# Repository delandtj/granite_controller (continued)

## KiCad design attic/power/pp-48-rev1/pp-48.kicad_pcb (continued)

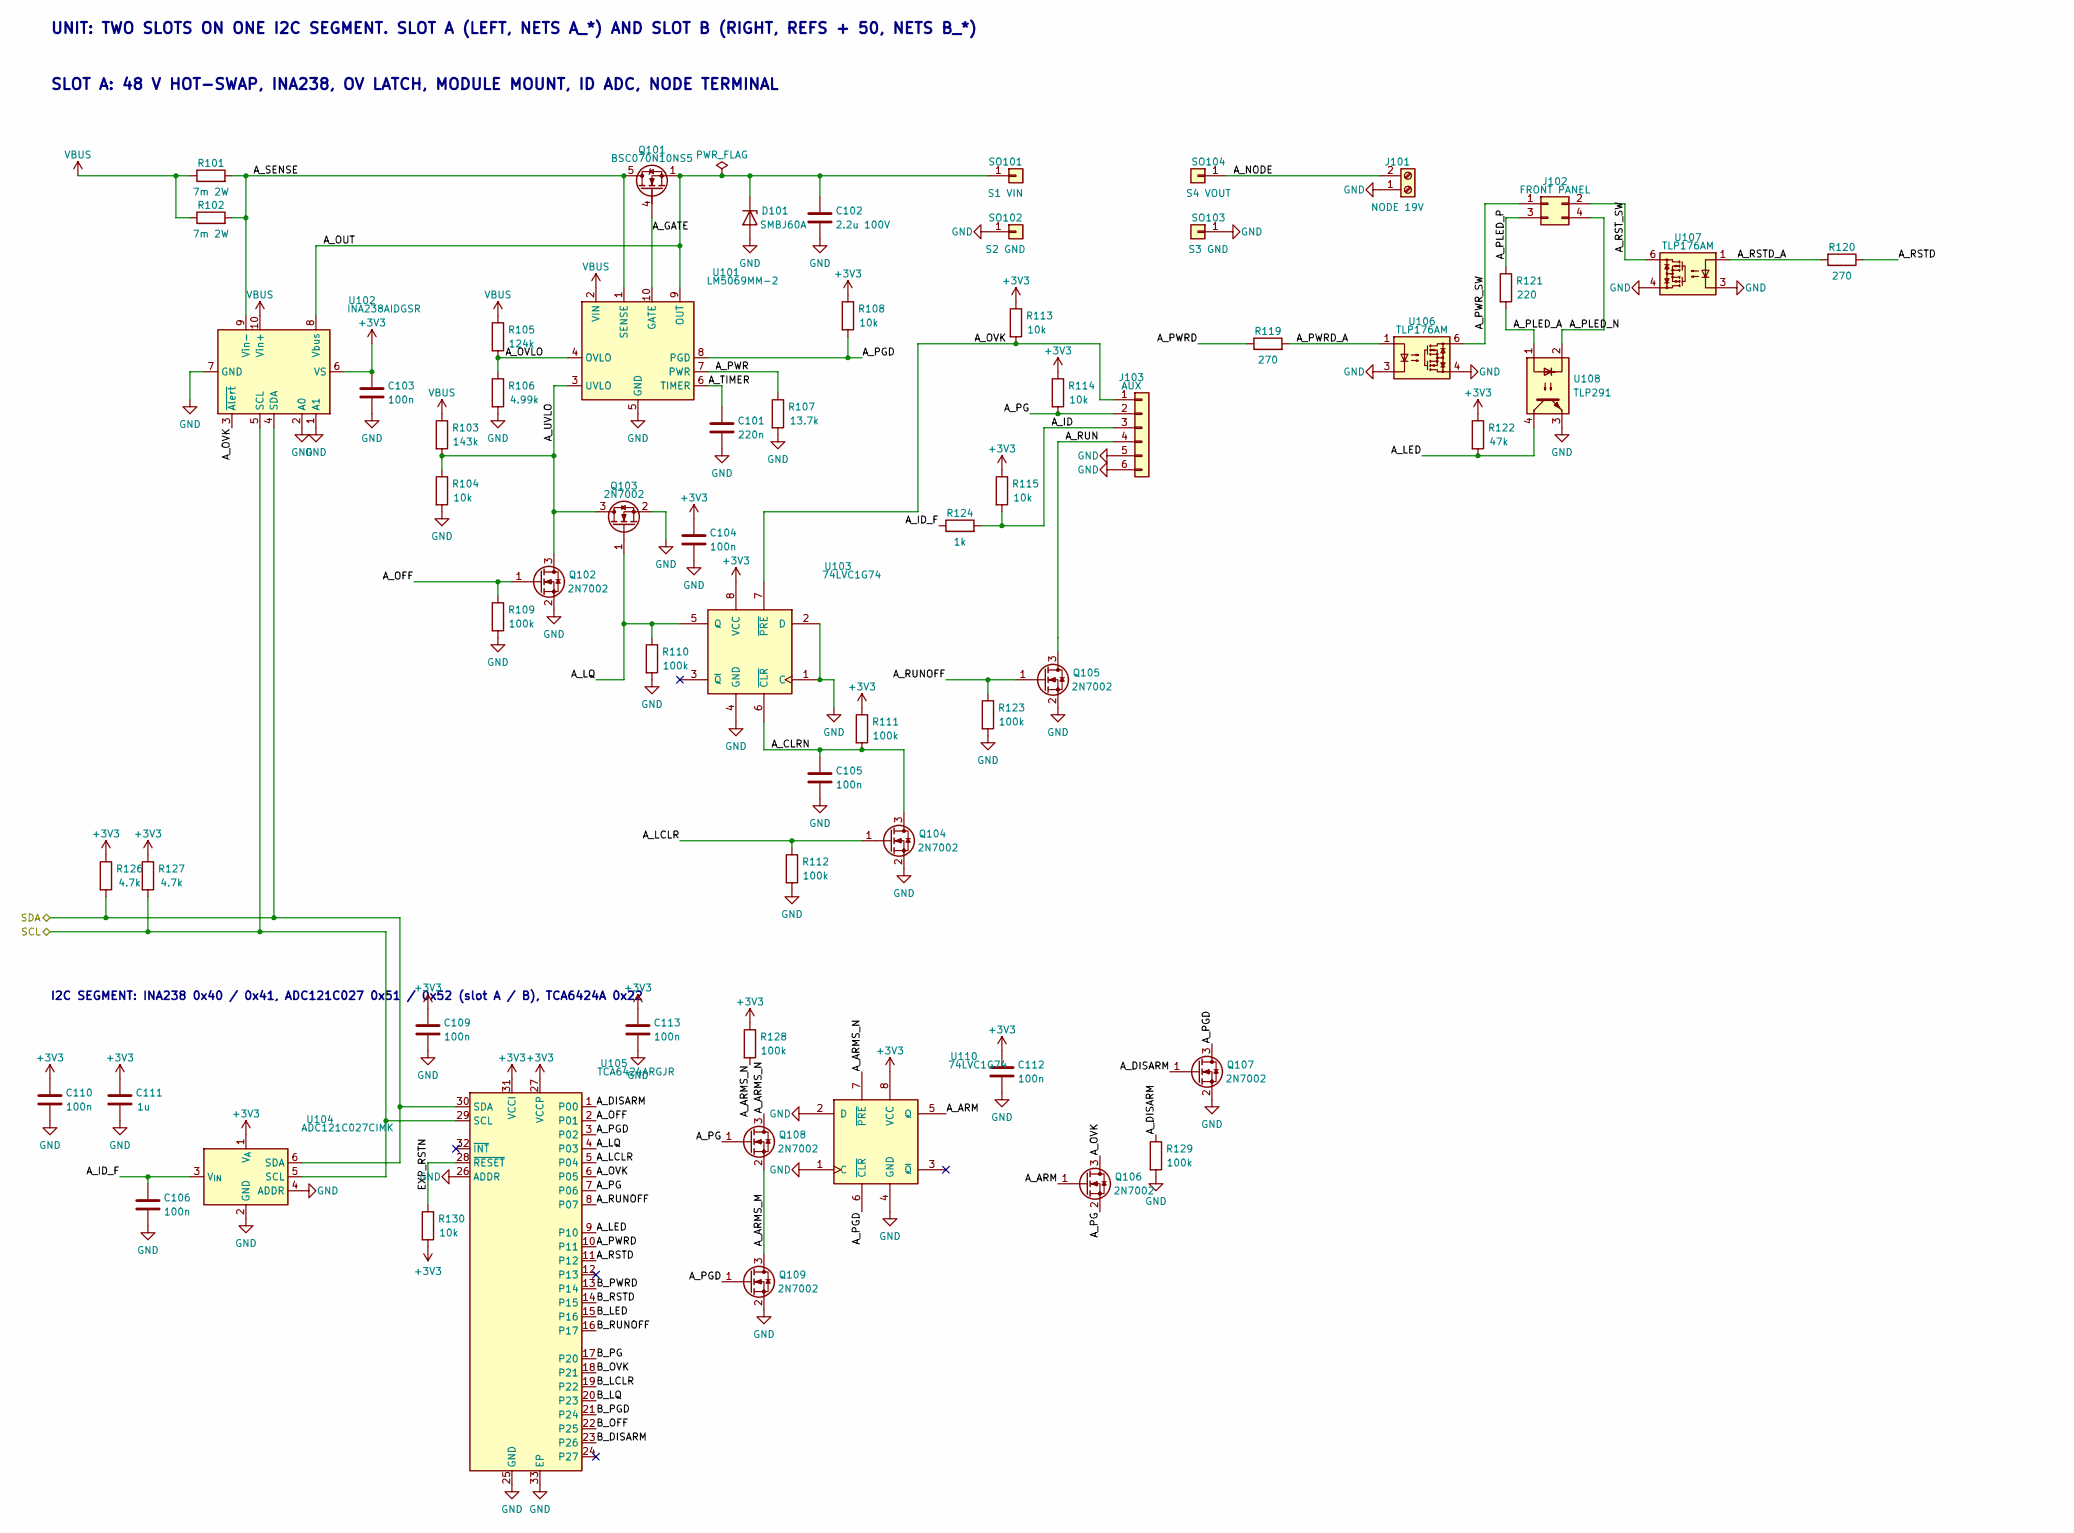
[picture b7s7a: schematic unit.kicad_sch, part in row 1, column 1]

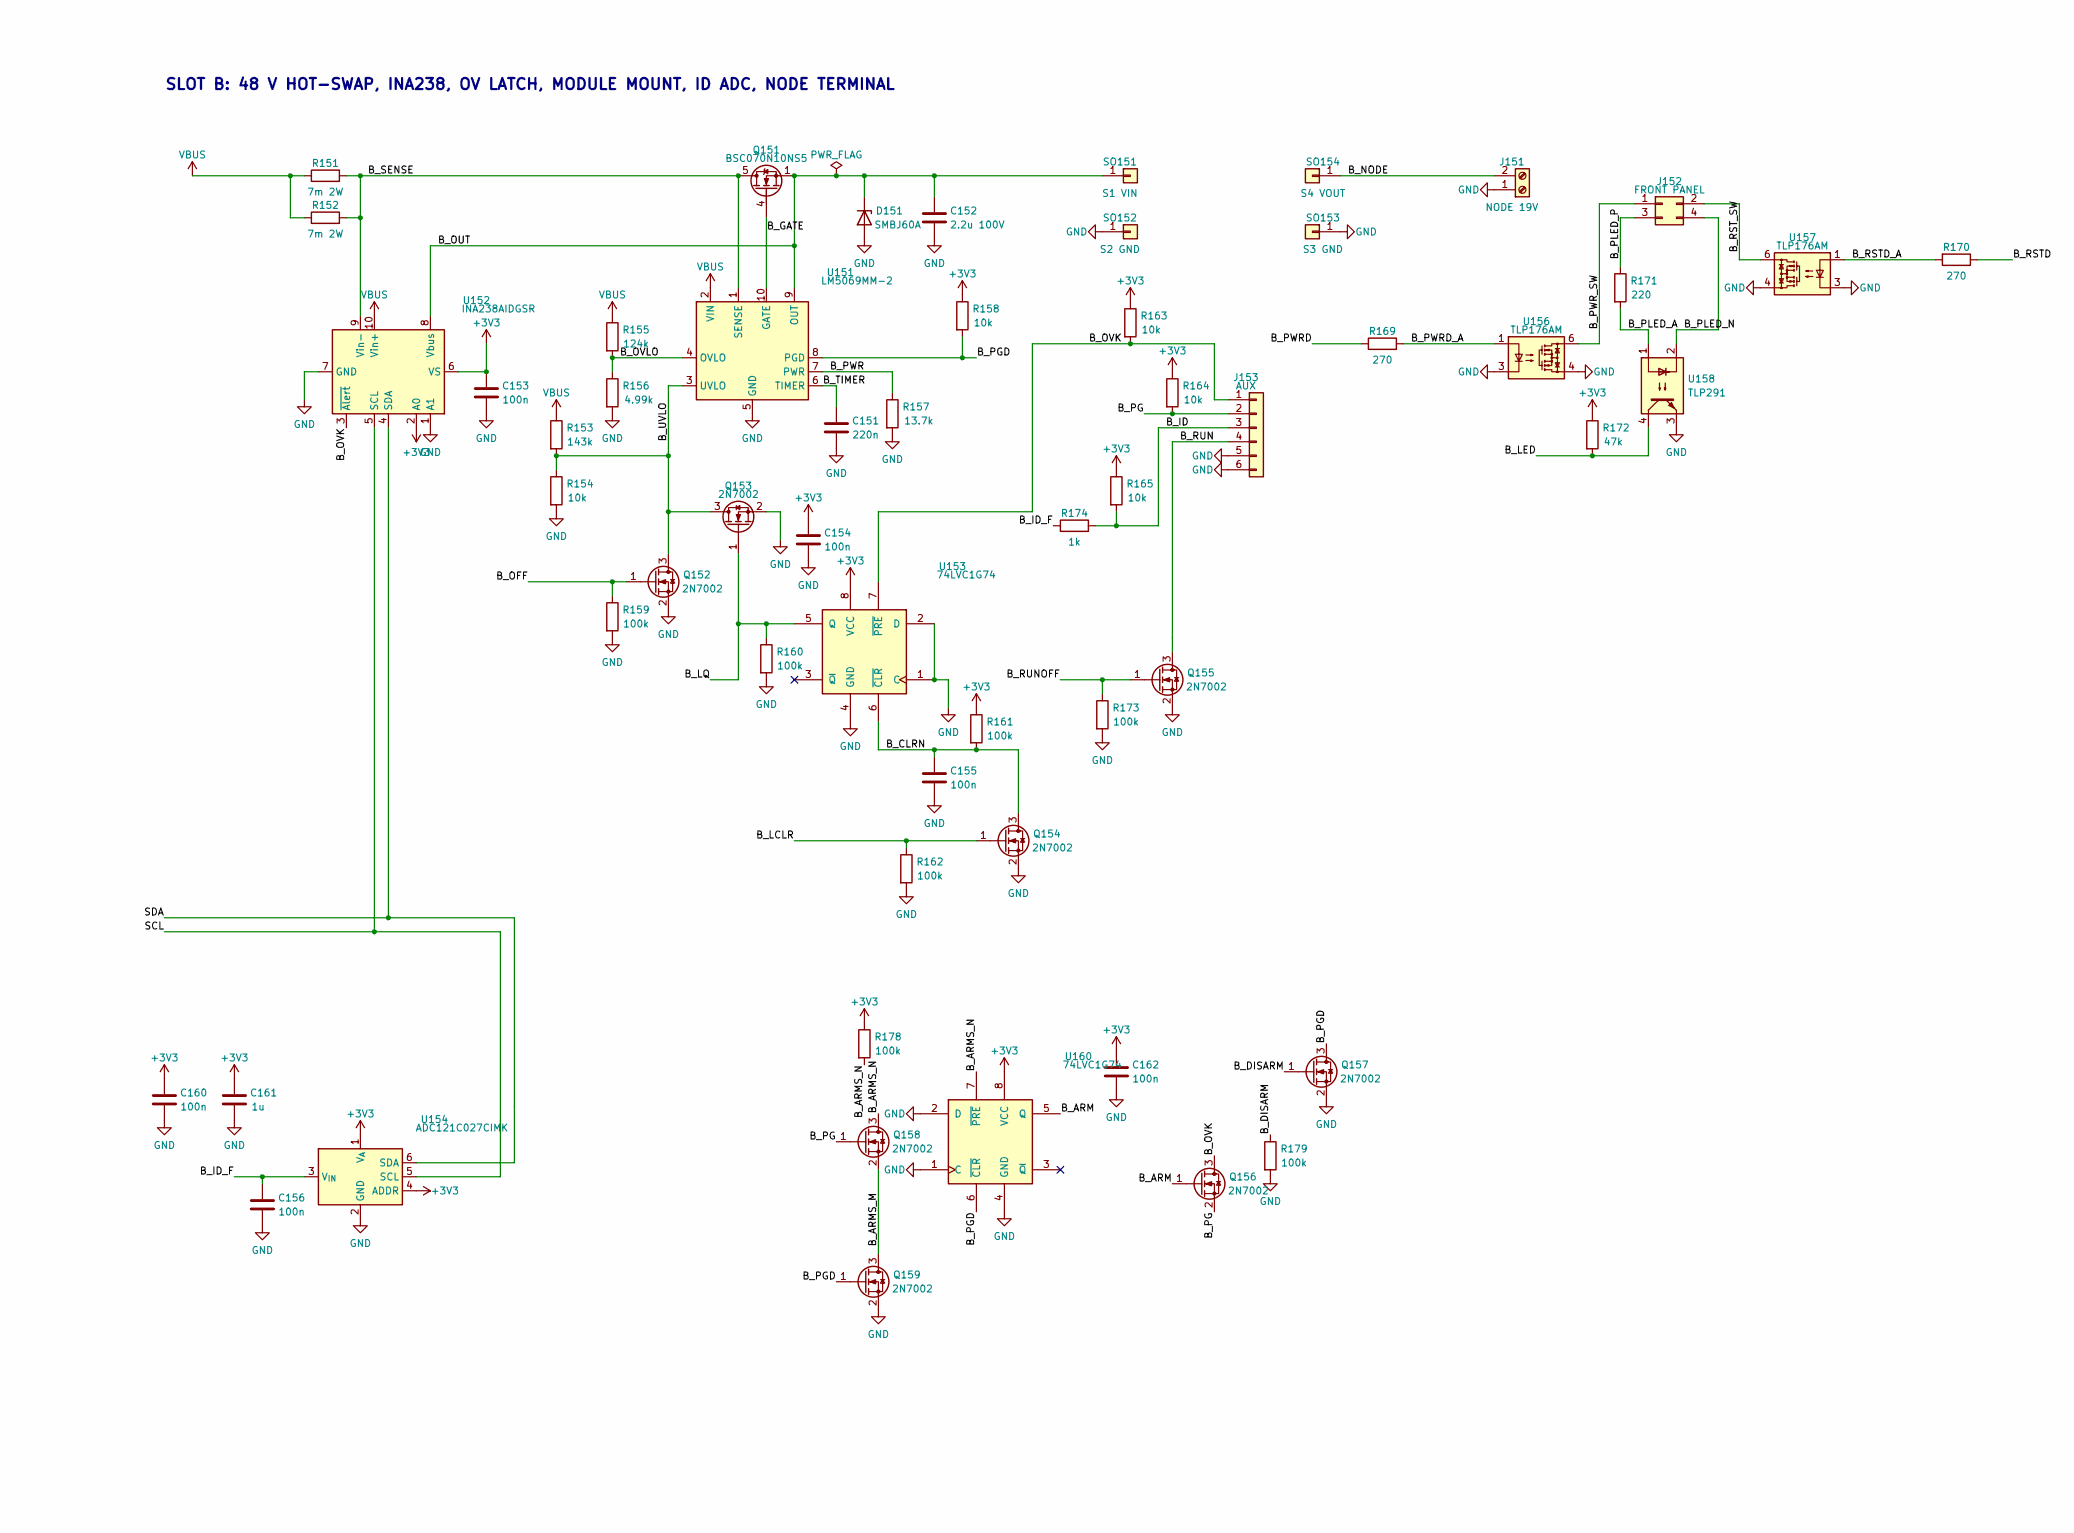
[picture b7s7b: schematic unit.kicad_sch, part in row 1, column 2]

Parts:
C101, C151: 220n; C_0603_1608Metric
C102, C152: 2.2u 100V; C_1210_3225Metric; LCSC C338133
C103, C104, C105, C106, C109, C110, C112, C113, C153, C154, C155, C156, C160, C162: 100n; C_0402_1005Metric; LCSC C1525
C111, C161: 1u; C_0402_1005Metric; LCSC C52923
D101, D151: SMBJ60A; D_SMB; LCSC C353345
J101, J151: NODE 19V; TerminalBlock_Degson_DG128-5.0-02P; MPN Degson DG128-5.0-02P-14-00A(H); LCSC C711349
J102, J152: FRONT PANEL; JST_GH_SM04B-GHS-TB_1x04-1MP_P1.25mm_Horizontal; MPN JST SM04B-GHS-TB; LCSC C189895
J103, J153: AUX; PM_Aux_Socket_2x03_P1.27; MPN hanxia HX PM1.27-2x3P TP; LCSC C41397112
Q101, Q151: BSC070N10NS5; TDSON-8-1
Q102, Q103, Q104, Q105, Q106, Q107, Q108, Q109, Q152, Q153, Q154, Q155, Q156, Q157, Q158, Q159: 2N7002; SOT-23; LCSC C8545
R101, R102, R151, R152: 7m 2W; R_2512_6332Metric; LCSC C2904232
R103, R153: 143k; R_0805_2012Metric
R104, R108, R113, R114, R115, R130, R154, R158, R163, R164, R165: 10k; R_0402_1005Metric; LCSC C25744
R105, R155: 124k; R_0805_2012Metric
R106, R156: 4.99k; R_0402_1005Metric
R107, R157: 13.7k; R_0402_1005Metric
R109, R110, R111, R112, R123, R128, R129, R159, R160, R161, R162, R173, R178, R179: 100k; R_0402_1005Metric; LCSC C25741
R119, R120, R169, R170: 270; R_0402_1005Metric; LCSC C22775
R121, R171: 220; R_0402_1005Metric; LCSC C25091
R122, R172: 47k; R_0402_1005Metric; LCSC C25792
R124, R174: 1k; R_0402_1005Metric; LCSC C11702
R126, R127: 4.7k; R_0402_1005Metric; LCSC C25900
SO101, SO151: S1 VIN; PM_Standoff_M2x7_SMTSO; MPN Sinhoo SMTSO2070CTJ; LCSC C2916355
SO102, SO152: S2 GND; PM_Standoff_M2x7_SMTSO; MPN Sinhoo SMTSO2070CTJ; LCSC C2916355
SO103, SO153: S3 GND; PM_Standoff_M2x7_SMTSO; MPN Sinhoo SMTSO2070CTJ; LCSC C2916355
SO104, SO154: S4 VOUT; PM_Standoff_M2x7_SMTSO; MPN Sinhoo SMTSO2070CTJ; LCSC C2916355
U101, U151: LM5069MM-2; MSOP-10_3x3mm_P0.5mm; LCSC C111822
U102, U152: INA238AIDGSR; TSSOP-10_3x3mm_P0.5mm
U103, U110, U153, U160: 74LVC1G74; VSSOP-8_2.3x2mm_P0.5mm; LCSC C70285
U104, U154: ADC121C027CIMK; TSOT-23-6; MPN TI ADC121C027CIMKX/NOPB; LCSC C2670157
U105: TCA6424ARGJR; VQFN-32-1EP_5x5mm_P0.5mm_EP3.15x3.15mm; LCSC C80692
U106, U107, U156, U157: TLP176AM; SOIC-4_4.55x3.7mm_P2.54mm; LCSC C5370540
U108, U158: TLP291; SOIC-4_4.55x2.6mm_P1.27mm; LCSC C55144

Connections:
+3V3: C103.1, C104.1, C109.1, C110.1, C111.1, C112.1, C113.1, C153.1, C154.1, C160.1, C161.1, C162.1, R108.1, R111.1, R113.1, R114.1, R115.1, R122.1, R126.1, R127.1, R128.1, R130.2, R158.1, R161.1, R163.1, R164.1, R165.1, R172.1, R178.1, U102.6 (VS), U103.8 (VCC), U104.1 (V_{A}), U105.27 (VCCP), U105.31 (VCCI), U110.8 (VCC), U152.2 (A0), U152.6 (VS), U153.8 (VCC), U154.1 (V_{A}), U154.4 (ADDR), U160.8 (VCC); also elsewhere on the board
/UNIT1_SCL: R127.2, U102.5 (SCL), U104.5 (SCL), U105.29 (SCL), U152.5 (SCL), U154.5 (SCL); also elsewhere on the board
/UNIT1_SDA: R126.2, U102.4 (SDA), U104.6 (SDA), U105.30 (SDA), U152.4 (SDA), U154.6 (SDA); also elsewhere on the board
/Unit 1/A_ARM: Q106.1 (G), U110.5 (Q)
/Unit 1/A_ARMS_M: Q108.2 (S), Q109.3 (D)
/Unit 1/A_ARMS_N: Q108.3 (D), R128.2, U110.7 (~PRE)
/Unit 1/A_CLRN: C105.1, Q104.3 (D), R111.2, U103.6 (~CLR)
/Unit 1/A_DISARM: Q107.1 (G), R129.1, U105.1 (P00); also elsewhere on the board
/Unit 1/A_GATE: Q101.4 (G), U101.10 (GATE)
/Unit 1/A_ID: J103.3, R115.2, R124.2
/Unit 1/A_ID_F: C106.1, R124.1, U104.3 (V_{IN})
/Unit 1/A_LCLR: Q104.1 (G), R112.1, U105.5 (P04); also elsewhere on the board
/Unit 1/A_LED: R122.2, U105.9 (P10), U108.4; also elsewhere on the board
/Unit 1/A_LQ: Q103.1 (G), R110.1, U103.5 (Q), U105.4 (P03); also elsewhere on the board
/Unit 1/A_NODE: J101.2, SO104.1
/Unit 1/A_OFF: Q102.1 (G), R109.1, U105.2 (P01); also elsewhere on the board
/Unit 1/A_OUT: C102.1, D101.1 (K), Q101.1 (S), Q101.2 (S), Q101.3 (S), SO101.1, U101.9 (OUT), U102.8 (Vbus)
/Unit 1/A_OVK: J103.1, Q106.3 (D), R113.2, U102.3 (~Alert), U103.7 (~PRE), U105.6 (P05); also elsewhere on the board
/Unit 1/A_OVLO: R105.2, R106.1, U101.4 (OVLO)
/Unit 1/A_PG: J103.2, Q106.2 (S), Q108.1 (G), R114.2, U105.7 (P06); also elsewhere on the board
/Unit 1/A_PGD: Q107.3 (D), Q109.1 (G), R108.2, U101.8 (PGD), U105.3 (P02), U110.6 (~CLR); also elsewhere on the board
/Unit 1/A_PLED_A: R121.2, U108.1
/Unit 1/A_PLED_N: J102.4, U108.2
/Unit 1/A_PLED_P: J102.3, R121.1
/Unit 1/A_PWR: R107.1, U101.7 (PWR)
/Unit 1/A_PWRD: R119.1, U105.10 (P11); also elsewhere on the board
/Unit 1/A_PWRD_A: R119.2, U106.1
/Unit 1/A_PWR_SW: J102.1, U106.6
/Unit 1/A_RSTD: R120.1, U105.11 (P12); also elsewhere on the board
/Unit 1/A_RSTD_A: R120.2, U107.1
/Unit 1/A_RST_SW: J102.2, U107.6
/Unit 1/A_RUN: J103.4, Q105.3 (D)
/Unit 1/A_RUNOFF: Q105.1 (G), R123.1, U105.8 (P07); also elsewhere on the board
/Unit 1/A_SENSE: Q101.5 (D), R101.2, R102.2, U101.1 (SENSE), U102.9 (Vin-)
/Unit 1/A_TIMER: C101.1, U101.6 (TIMER)
/Unit 1/A_UVLO: Q102.3 (D), Q103.3 (D), R103.2, R104.1, U101.3 (UVLO)
/Unit 1/B_ARM: Q156.1 (G), U160.5 (Q)
/Unit 1/B_ARMS_M: Q158.2 (S), Q159.3 (D)
/Unit 1/B_ARMS_N: Q158.3 (D), R178.2, U160.7 (~PRE)
/Unit 1/B_CLRN: C155.1, Q154.3 (D), R161.2, U153.6 (~CLR)
/Unit 1/B_DISARM: Q157.1 (G), R179.1, U105.23 (P26)
/Unit 1/B_GATE: Q151.4 (G), U151.10 (GATE)
/Unit 1/B_ID: J153.3, R165.2, R174.2
/Unit 1/B_ID_F: C156.1, R174.1, U154.3 (V_{IN})
/Unit 1/B_LCLR: Q154.1 (G), R162.1, U105.19 (P22)
/Unit 1/B_LED: R172.2, U105.15 (P16), U158.4
/Unit 1/B_LQ: Q153.1 (G), R160.1, U105.20 (P23), U153.5 (Q)
/Unit 1/B_NODE: J151.2, SO154.1
/Unit 1/B_OFF: Q152.1 (G), R159.1, U105.22 (P25)
/Unit 1/B_OUT: C152.1, D151.1 (K), Q151.1 (S), Q151.2 (S), Q151.3 (S), SO151.1, U151.9 (OUT), U152.8 (Vbus)
/Unit 1/B_OVK: J153.1, Q156.3 (D), R163.2, U105.18 (P21), U152.3 (~Alert), U153.7 (~PRE)
/Unit 1/B_OVLO: R155.2, R156.1, U151.4 (OVLO)
/Unit 1/B_PG: J153.2, Q156.2 (S), Q158.1 (G), R164.2, U105.17 (P20)
/Unit 1/B_PGD: Q157.3 (D), Q159.1 (G), R158.2, U105.21 (P24), U151.8 (PGD), U160.6 (~CLR)
/Unit 1/B_PLED_A: R171.2, U158.1
/Unit 1/B_PLED_N: J152.4, U158.2
/Unit 1/B_PLED_P: J152.3, R171.1
/Unit 1/B_PWR: R157.1, U151.7 (PWR)
/Unit 1/B_PWRD: R169.1, U105.13 (P14)
/Unit 1/B_PWRD_A: R169.2, U156.1
/Unit 1/B_PWR_SW: J152.1, U156.6
/Unit 1/B_RSTD: R170.1, U105.14 (P15)
/Unit 1/B_RSTD_A: R170.2, U157.1
/Unit 1/B_RST_SW: J152.2, U157.6
/Unit 1/B_RUN: J153.4, Q155.3 (D)
/Unit 1/B_RUNOFF: Q155.1 (G), R173.1, U105.16 (P17)
/Unit 1/B_SENSE: Q151.5 (D), R151.2, R152.2, U151.1 (SENSE), U152.9 (Vin-)
/Unit 1/B_TIMER: C151.1, U151.6 (TIMER)
/Unit 1/B_UVLO: Q152.3 (D), Q153.3 (D), R153.2, R154.1, U151.3 (UVLO)
/Unit 1/EXP_RSTN: R130.1, U105.28 (~RESET)
GND: C101.2, C102.2, C103.2, C104.2, C105.2, C106.2, C109.2, C110.2, C111.2, C112.2, C113.2, C151.2, C152.2, C153.2, C154.2, C155.2, C156.2, C160.2, C161.2, C162.2, D101.2 (A), D151.2 (A), J101.1, J103.5, J103.6, J151.1, J153.5, J153.6, Q102.2 (S), Q103.2 (S), Q104.2 (S), Q105.2 (S), Q107.2 (S), Q109.2 (S), Q152.2 (S), Q153.2 (S), Q154.2 (S), Q155.2 (S), Q157.2 (S), Q159.2 (S), R104.2, R106.2, R107.2, R109.2, R110.2, R112.2, R123.2, R129.2, R154.2, R156.2, R157.2, R159.2, R160.2, R162.2, R173.2, R179.2, SO102.1, SO103.1, SO152.1, SO153.1, U101.5 (GND), U102.1 (A1), U102.2 (A0), U102.7 (GND), U103.1 (C), U103.2 (D), U103.4 (GND), U104.2 (GND), U104.4 (ADDR), U105.25 (GND), U105.26 (ADDR), U105.33 (EP), U106.3, U106.4, U107.3, U107.4, U108.3, U110.1 (C), U110.2 (D), U110.4 (GND), U151.5 (GND), U152.1 (A1), U152.7 (GND), U153.1 (C), U153.2 (D), U153.4 (GND), U154.2 (GND), U156.3, U156.4, U157.3, U157.4, U158.3, U160.1 (C), U160.2 (D), U160.4 (GND); also elsewhere on the board
VBUS: R101.1, R102.1, R103.1, R105.1, R151.1, R152.1, R153.1, R155.1, U101.2 (VIN), U102.10 (Vin+), U151.2 (VIN), U152.10 (Vin+); also elsewhere on the board

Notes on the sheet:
SLOT A: 48 V HOT-SWAP, INA238, OV LATCH, MODULE MOUNT, ID ADC, NODE TERMINAL
SLOT B: 48 V HOT-SWAP, INA238, OV LATCH, MODULE MOUNT, ID ADC, NODE TERMINAL
UNIT: TWO SLOTS ON ONE I2C SEGMENT. SLOT A (LEFT, NETS A_*) AND SLOT B (RIGHT, REFS + 50, NETS B_*)
I2C SEGMENT: INA238 0x40 / 0x41, ADC121C027 0x51 / 0x52 (slot A / B), TCA6424A 0x22

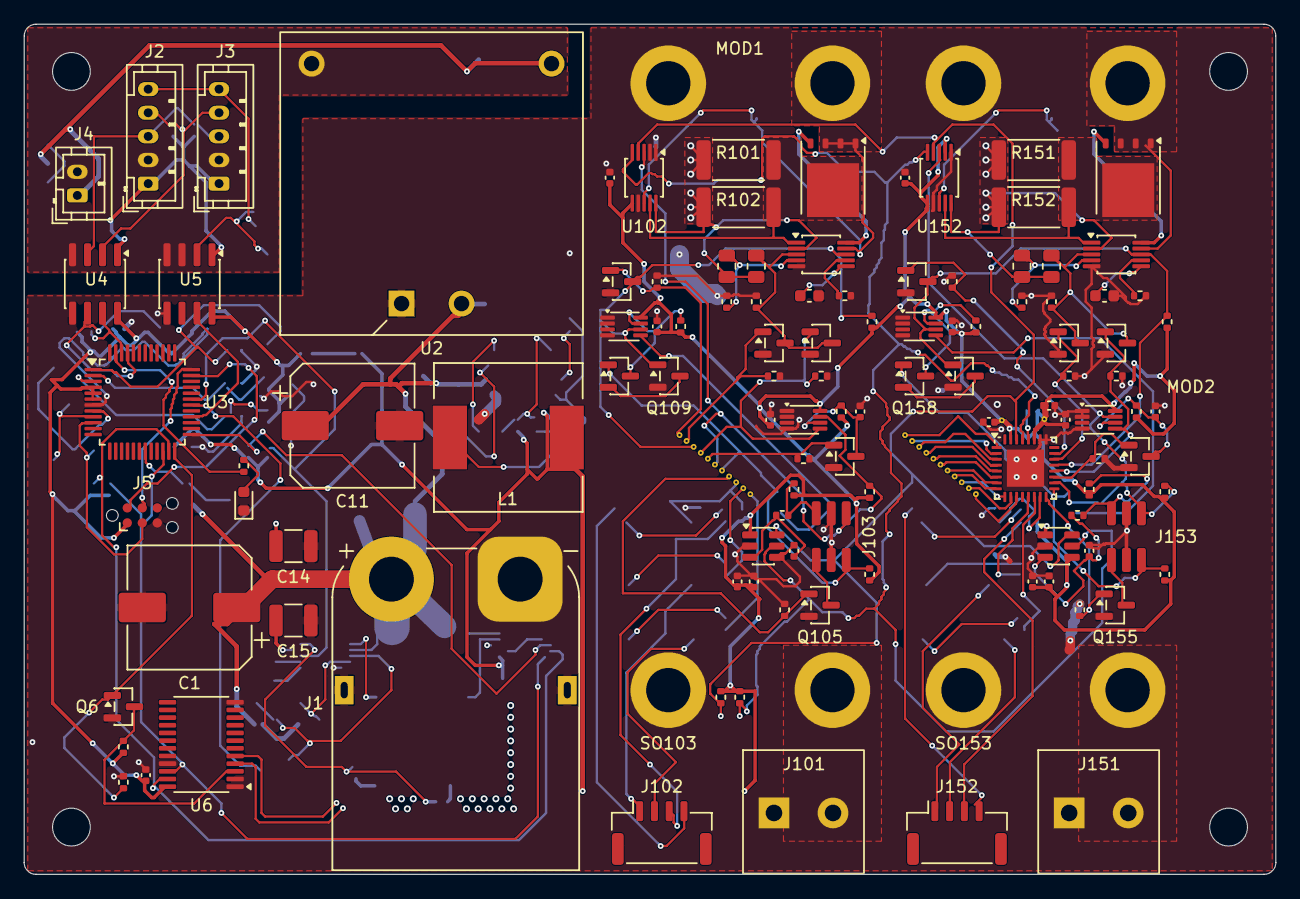
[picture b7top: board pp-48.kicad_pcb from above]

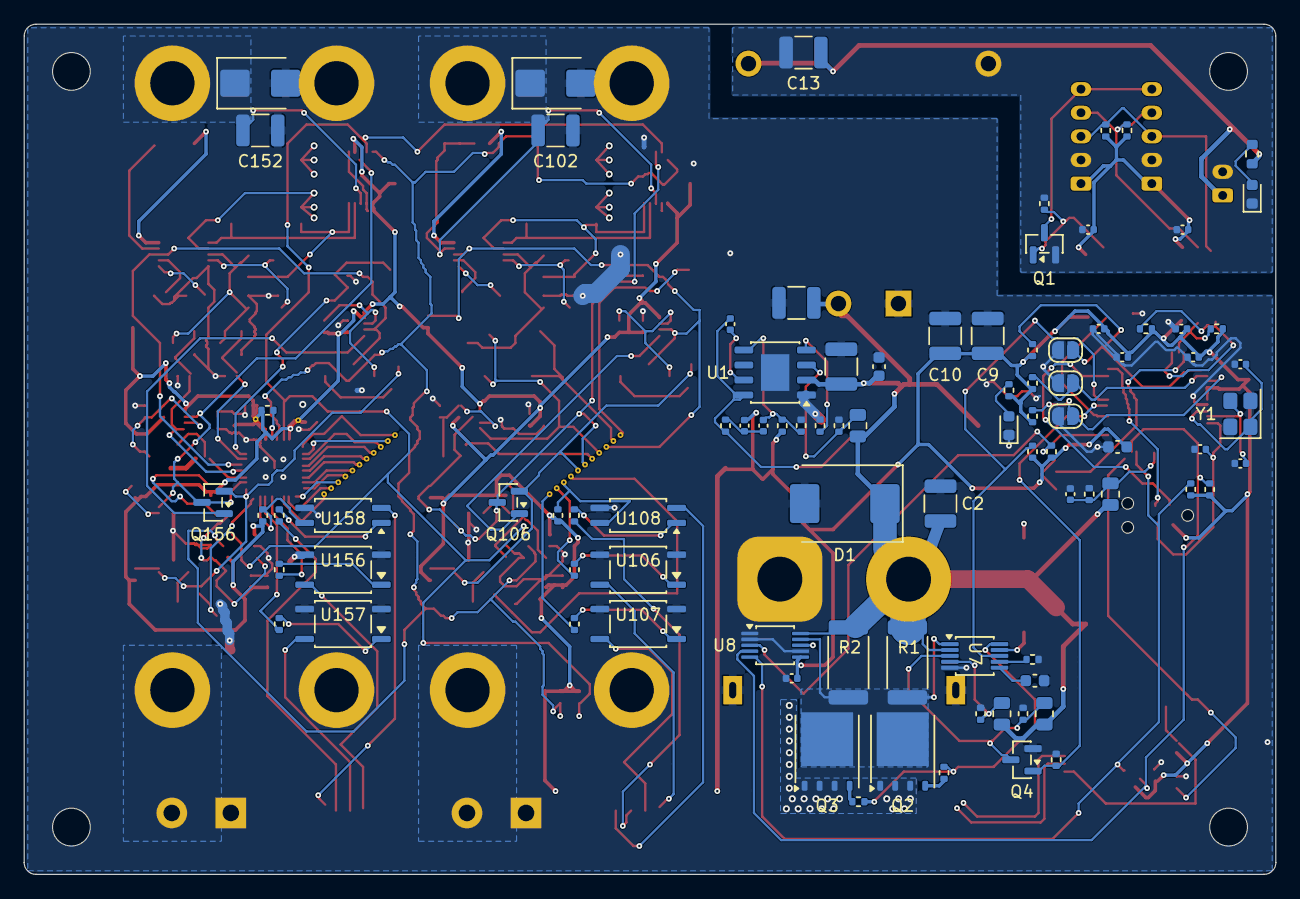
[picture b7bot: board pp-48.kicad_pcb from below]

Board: 4 copper layers, 106.0 x 72.0 mm, 240 parts (90 on the bottom side), 117 nets.

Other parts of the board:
BV100, BV101, BV102, BV103, BV104, BV105, BV106, BV107, BV108, BV109, BV110, BV150, BV151, BV152, BV153, BV154, BV155, BV156, BV157, BV158, BV159, BV160: (no value)
H1, H2, H3, H4: MountingHole_3.2mm_M3
MOD1, MOD2: PM_Module_Outline
PV1B3, PV1B4: (no value)

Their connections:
+3V3: PV1B3.1, PV1B4.1; also elsewhere on the board
/Unit 1/A_DISARM: BV100.1, BV150.1; also elsewhere on the board
/Unit 1/A_LCLR: BV104.1, BV154.1; also elsewhere on the board
/Unit 1/A_LED: BV108.1, BV158.1; also elsewhere on the board
/Unit 1/A_LQ: BV103.1, BV153.1; also elsewhere on the board
/Unit 1/A_OFF: BV101.1, BV151.1; also elsewhere on the board
/Unit 1/A_OVK: BV105.1, BV155.1; also elsewhere on the board
/Unit 1/A_PG: BV106.1, BV156.1; also elsewhere on the board
/Unit 1/A_PGD: BV102.1, BV152.1; also elsewhere on the board
/Unit 1/A_PWRD: BV109.1, BV159.1; also elsewhere on the board
/Unit 1/A_RSTD: BV110.1, BV160.1; also elsewhere on the board
/Unit 1/A_RUNOFF: BV107.1, BV157.1; also elsewhere on the board

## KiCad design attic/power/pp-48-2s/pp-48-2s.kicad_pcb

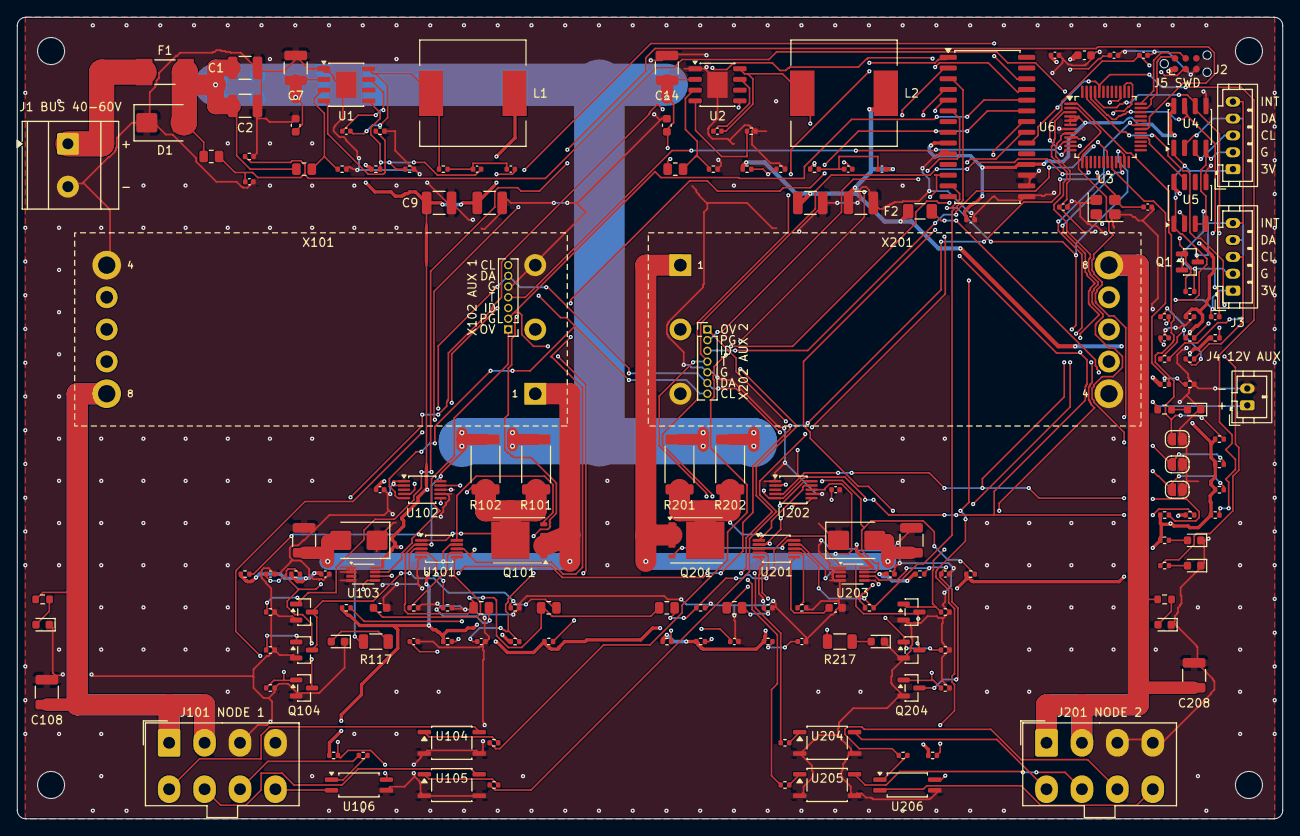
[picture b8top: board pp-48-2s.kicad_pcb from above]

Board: 4 copper layers, 150.0 x 95.0 mm, 178 parts (0 on the bottom side), 102 nets.

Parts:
C1, C2, C7, C14, C102, C202: 2.2u 100V; C_1210_3225Metric
C3: 10n; C_0402_1005Metric
C4, C11: 2.2n 50V; C_0402_1005Metric
C5: 1.5n; C_0402_1005Metric
C6, C13, C18, C20, C21, C24, C25, C26, C27, C28, C103, C104, C105, C106, C107, C203, C204, C205, C206, C207: 100n; C_0402_1005Metric
C8, C15: 100n 100V; C_0603_1608Metric
C9, C10: 22u 10V; C_1210_3225Metric
C12: 2.2n; C_0402_1005Metric
C16, C17: 22u 25V; C_1210_3225Metric
C19: 4.7u; C_0603_1608Metric
C22, C23: 33p; C_0402_1005Metric
C101, C201: 220n; C_0603_1608Metric
C108, C208: 2.2u 50V; C_1210_3225Metric
D1, D101, D201: SMBJ60A; D_SMB
D2: GREEN 12V; LED_0603_1608Metric
D3: GREEN 3V3; LED_0603_1608Metric
D4: GREEN RUN; LED_0603_1608Metric
D102, D202: GREEN ON; LED_0603_1608Metric
D103, D203: GREEN NODE; LED_0603_1608Metric
F1: 10A nano2; Fuse_Littelfuse-NANO2-451_453
F2: 1.5A; Fuse_1206_3216Metric
H1, H2, H3, H4: MountingHole_3.2mm_M3
J1: BUS 40-60V; TerminalBlock_Phoenix_MKDS-3-2-5.08_1x02_P5.08mm_Horizontal
J2: CTRL IN; JST_PH_B5B-PH-K_1x05_P2.00mm_Vertical
J3: CTRL OUT; JST_PH_B5B-PH-K_1x05_P2.00mm_Vertical
J4: 12V AUX OUT; JST_PH_B2B-PH-K_1x02_P2.00mm_Vertical
J5: SWD; Tag-Connect_TC2030-IDC-NL_2x03_P1.27mm_Vertical
J101, J201: NODE; Molex_Mini-Fit_Jr_5566-08A_2x04_P4.20mm_Vertical
JP1: ADR0; SolderJumper-2_P1.3mm_Open_RoundedPad1.0x1.5mm
JP2: ADR1; SolderJumper-2_P1.3mm_Open_RoundedPad1.0x1.5mm
JP3: ADR2; SolderJumper-2_P1.3mm_Open_RoundedPad1.0x1.5mm
L1: 33u; L_12x12mm_H6mm
L2: 68u; L_12x12mm_H6mm
Q1, Q102, Q103, Q104, Q202, Q203, Q204: 2N7002; SOT-23
Q101, Q201: BSC070N10NS5; TDSON-8-1
R1: 470k; R_0805_2012Metric
R2: 13k; R_0402_1005Metric
R3, R9: 1M; R_0805_2012Metric
R4, R10: 52.3k; R_0402_1005Metric
R5: 41.2k; R_0402_1005Metric
R6: 86.6k; R_0402_1005Metric
R7, R13: 49.9k; R_0402_1005Metric
R8, R12, R14: 453k; R_0402_1005Metric
R11, R15, R20, R21, R22, R30, R109, R110, R111, R112, R209, R210, R211, R212: 100k; R_0402_1005Metric
R16: 27k; R_0402_1005Metric
R17: 4.7k; R_0603_1608Metric
R18, R19: 1k; R_0402_1005Metric
R23, R24: 2.2k; R_0402_1005Metric
R25, R104, R106, R108, R113, R114, R115, R116, R204, R206, R208, R213, R214, R215, R216: 10k; R_0402_1005Metric
R26, R27, R28, R29: 4.7k; R_0402_1005Metric
R101, R102, R201, R202: 7m 2W; R_2512_6332Metric
R103, R203: 143k; R_0805_2012Metric
R105, R205: 240k; R_0805_2012Metric
R107, R207: 13.7k; R_0402_1005Metric
R117, R217: 47k; R_1206_3216Metric
R118, R218: 10k; R_0603_1608Metric
R119, R120, R219, R220: 270; R_0402_1005Metric
R121, R221: 220; R_0402_1005Metric
R122, R222: 47k; R_0402_1005Metric
U1, U2: LM5164DDA; HSOP-8-1EP_3.9x4.9mm_P1.27mm_EP2.41x3.1mm
U3: STM32G070CBT6; LQFP-48_7x7mm_P0.5mm
U4: ISO1640BD; SOIC-8_3.9x4.9mm_P1.27mm
U5: ISO7721D; SOIC-8_3.9x4.9mm_P1.27mm
U6: MCP23017-E/SO; SOIC-28W_7.5x17.9mm_P1.27mm
U101, U201: LM5069MM-2; MSOP-10_3x3mm_P0.5mm
U102, U202: INA238AIDGSR; TSSOP-10_3x3mm_P0.5mm
U103, U203: 74LVC1G74; VSSOP-8_2.3x2mm_P0.5mm
U104, U105, U204, U205: TLP176AM; SOIC-4_4.55x3.7mm_P2.54mm
U106, U206: TLP291; SOIC-4_4.55x2.6mm_P1.27mm
X101, X201: PM-19V-200W; Brick_Eighth_DOSA_Plane
X102, X202: J2 AUX; PinHeader_1x07_P1.27mm_Vertical
Y1: 8MHz; Crystal_SMD_3225-4Pin_3.2x2.5mm

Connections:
+3V3: C5.2, C9.1, C10.1, C18.1, C19.1, C20.1, C25.1, C27.1, C28.1, C103.1, C104.1, C203.1, C204.1, J5.1, L1.2, R6.1, R18.1, R20.1, R21.1, R22.1, R23.1, R24.1, R25.1, R26.1, R27.1, R108.1, R111.1, R113.1, R114.1, R115.1, R116.1, R122.1, R208.1, R211.1, R213.1, R214.1, R215.1, R216.1, R222.1, U3.4, U3.5, U3.6, U4.8, U5.8, U6.9, U6.18, U102.6, U103.8, U202.2, U202.6, U203.8
+12V: C12.2, C16.1, C17.1, F2.1, L2.2, R12.1, R15.1
/AUX_SNS: R15.2, R16.1, U3.20
/Bucks/BST1: C4.1, U1.7
/Bucks/BST2: C11.1, U2.7
/Bucks/EN1: R3.2, R4.1, U1.3
/Bucks/EN2: R9.2, R10.1, U2.3
/Bucks/FB1: C6.2, R6.2, R7.1, U1.5
/Bucks/FB2: C13.2, R12.2, R13.1, U2.5
/Bucks/INJ1: C5.1, C6.1, R8.2
/Bucks/INJ2: C12.1, C13.1, R14.2
/Bucks/LED12_A: D2.2, R17.2
/Bucks/LED33_A: D3.2, R18.2
/Bucks/RON1: R5.1, U1.4
/Bucks/RON2: R11.1, U2.4
/Bucks/SW1: C4.2, L1.1, R8.1, U1.8
/Bucks/SW2: C11.2, L2.1, R14.1, U2.8
/Bucks/V12_OUT: F2.2, J4.1, R17.1
/EXP_IRQ: R25.2, U3.44, U6.20
/INT_OUT: U3.28, U5.7
/Input/VBUS_IN: F1.1, J1.1
/Link/CTRL_INT: J2.5, J3.5, Q1.3
/Link/CTRL_SCL: J2.3, J3.3, R29.2, U4.3
/Link/CTRL_SDA: J2.4, J3.4, R28.2, U4.2
/Link/ISO_OUTA: Q1.1, R30.1, U5.2
/MCU/ADR0: JP1.1, R20.2, U3.1
/MCU/ADR1: JP2.1, R21.2, U3.2
/MCU/ADR2: JP3.1, R22.2, U3.3
/MCU/LEDRUN_A: D4.2, R19.2
/MCU/LED_RUN: R19.1, U3.47
/MCU/NRST: C21.1, J5.3, U3.10
/MCU/OSC_IN: C22.1, U3.8, Y1.1
/MCU/OSC_OUT: C23.1, U3.9, Y1.3
/MCU/SWCLK: J5.4, U3.36
/MCU/SWDIO: J5.2, U3.35
/S1_ID: C106.1, R115.2, U3.11, X102.3
/S1_LCLR: Q104.1, R112.1, U3.31
/S1_LED: R122.2, U6.26, U106.4
/S1_LQ: Q103.1, R110.1, U6.25, U103.5
/S1_OFF: Q102.1, R109.1, U3.30
/S1_PG: R114.2, U6.24, X102.2
/S1_PGD: R108.2, U6.23, U101.8
/S1_PWRD: R119.1, U6.21
/S1_RSTD: R120.1, U6.22
/S1_TEMP: C107.1, R116.2, U3.12, X102.4
/S2_ID: C206.1, R215.2, U3.13, X202.3
/S2_LCLR: Q204.1, R212.1, U3.39
/S2_LED: R222.2, U6.6, U206.4
/S2_LQ: Q203.1, R210.1, U6.5, U203.5
/S2_OFF: Q202.1, R209.1, U3.38
/S2_PG: R214.2, U6.4, X202.2
/S2_PGD: R208.2, U6.3, U201.8
/S2_PWRD: R219.1, U6.1
/S2_RSTD: R220.1, U6.2
/S2_TEMP: C207.1, R216.2, U3.14, X202.4
/SCL1: R27.2, U3.45, U4.6
/SCL2: R24.2, U3.22, U6.12, U102.5, U202.5, X102.7, X202.7
/SDA1: R26.2, U3.46, U4.7
/SDA2: R23.2, U3.23, U6.13, U102.4, U202.4, X102.6, X202.6
/Slot 1/CLRN: C105.1, Q104.3, R111.2, U103.6
/Slot 1/GATE: Q101.4, U101.10
/Slot 1/NL_A: D103.2, R118.2
/Slot 1/NODE: C108.1, J101.1, J101.2, R118.1, X101.8
/Slot 1/ONL_A: D102.2, R117.2
/Slot 1/OUT: C102.1, D101.2, Q101.1, Q101.2, Q101.3, R117.1, U101.9, U102.8, X101.1
/Slot 1/OVK: R113.2, U103.7, X102.1
/Slot 1/OVLO: R105.2, R106.1, U101.4
/Slot 1/PLED_A: R121.2, U106.1
/Slot 1/PLED_N: J101.8, U106.2
/Slot 1/PLED_P: J101.7, R121.1
/Slot 1/PWR: R107.1, U101.7
/Slot 1/PWRD_A: R119.2, U104.1
/Slot 1/PWR_SW: J101.5, U104.6
/Slot 1/RSTD_A: R120.2, U105.1
/Slot 1/RST_SW: J101.6, U105.6
/Slot 1/SENSE: Q101.5, R101.2, R102.2, U101.1, U102.9
/Slot 1/TIMER: C101.1, U101.6
/Slot 1/UVLO: Q102.3, Q103.3, R103.2, R104.1, U101.3
/Slot 2/CLRN: C205.1, Q204.3, R211.2, U203.6
/Slot 2/GATE: Q201.4, U201.10
/Slot 2/NL_A: D203.2, R218.2
/Slot 2/NODE: C208.1, J201.1, J201.2, R218.1, X201.8
/Slot 2/ONL_A: D202.2, R217.2
/Slot 2/OUT: C202.1, D201.2, Q201.1, Q201.2, Q201.3, R217.1, U201.9, U202.8, X201.1
/Slot 2/OVK: R213.2, U203.7, X202.1
/Slot 2/OVLO: R205.2, R206.1, U201.4
/Slot 2/PLED_A: R221.2, U206.1
/Slot 2/PLED_N: J201.8, U206.2
/Slot 2/PLED_P: J201.7, R221.1
/Slot 2/PWR: R207.1, U201.7
/Slot 2/PWRD_A: R219.2, U204.1
/Slot 2/PWR_SW: J201.5, U204.6
/Slot 2/RSTD_A: R220.2, U205.1
/Slot 2/RST_SW: J201.6, U205.6
/Slot 2/SENSE: Q201.5, R201.2, R202.2, U201.1, U202.9
/Slot 2/TIMER: C201.1, U201.6
/Slot 2/UVLO: Q202.3, Q203.3, R203.2, R204.1, U201.3
/VBUS_SNS: C3.1, R1.2, R2.1, U3.19
CTRL_3V3: C24.1, C26.1, J2.1, J3.1, R28.1, R29.1, U4.1, U5.1
CTRL_GND: C24.2, C26.2, J2.2, J3.2, Q1.2, R30.2, U4.4, U5.3, U5.4
GND: C1.2, C2.2, C3.2, C7.2, C8.2, C9.2, C10.2, C14.2, C15.2, C16.2, C17.2, C18.2, C19.2, C20.2, C21.2, C22.2, C23.2, C25.2, C27.2, C28.2, C101.2, C102.2, C103.2, C104.2, C105.2, C106.2, C107.2, C108.2, C201.2, C202.2, C203.2, C204.2, C205.2, C206.2, C207.2, C208.2, D1.1, D2.1, D3.1, D4.1, D101.1, D102.1, D103.1, D201.1, D202.1, D203.1, J1.2, J4.2, J5.5, J101.3, J101.4, J201.3, J201.4, JP1.2, JP2.2, JP3.2, Q102.2, Q103.2, Q104.2, Q202.2, Q203.2, Q204.2, R2.2, R4.2, R5.2, R7.2, R10.2, R11.2, R13.2, R16.2, R104.2, R106.2, R107.2, R109.2, R110.2, R112.2, R204.2, R206.2, R207.2, R209.2, R210.2, R212.2, U1.1, U1.9, U2.1, U2.9, U3.7, U4.5, U5.5, U6.10, U6.15, U6.16, U6.17, U101.5, U102.1, U102.2, U102.7, U103.1, U103.2, U103.4, U104.3, U104.4, U105.3, U105.4, U106.3, U201.5, U202.1, U202.7, U203.1, U203.2, U203.4, U204.3, U204.4, U205.3, U205.4, U206.3, X101.3, X101.4, X102.5, X201.3, X201.4, X202.5, Y1.2, Y1.4
VBUS: C1.1, C2.1, C7.1, C8.1, C14.1, C15.1, D1.2, F1.2, R1.1, R3.1, R9.1, R101.1, R102.1, R103.1, R105.1, R201.1, R202.1, R203.1, R205.1, U1.2, U2.2, U101.2, U102.10, U201.2, U202.10
